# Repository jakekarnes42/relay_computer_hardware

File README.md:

# Relay Computer (Hardware)
This repo contains the hardware information for a computer constructed out of relays. Its software companion project can be found [here](https://github.com/jakekarnes42/relay_computer_software). 

This project has taken much of its inspiration from Dr. Harry Porter's [relay computer](https://web.cecs.pdx.edu/~harry/Relay/RelayPaper.htm). While there are many architectural similarities, there are also significant differences which are described below. This project wouldn't have been possible for me without his clear notes and thorough explanations. 

The documentation is still a work in progress and likely to change as the design itself changes. 

## Hardware Architecture Notes:
### Registers:
All registers are 16 bits (1 word) wide. There are 11 registers total.

There are 5 general purpose registers: AX, BX, CX, DX, and EX. These registers don’t have any special functions (e.g. stack operations). 

There are 2 stack-pointer registers: SP and RP. These are used with the PUSH, POP, CALL and CALL_I operations. These registers point to memory locations of the current top of the stack. When a value is pushed onto the stack, the register is first incremented, and then the value is copied to that location in memory. When a value is to popped off the stack, the value in the memory address pointed to by the stack register is returned, and then the stack register is decremented. 

There is one program counter: PC. The PC contains the address of the next
instruction to be executed. In some computers, this register is called the “Instruction Pointer”.

There is one instruction register: INST. During instruction execution, INST contains the current instruction being executed.

There are two temporary registers: TMP1 and TMP2. These are considered “scratch pads” and their values are not to be considered consistent between instructions. These are the inputs to the ALU. 
### Condition Codes:
####  Zero: 
True (1) when the ALU output is zero. If any bit of the ALU output is 1, then this flag will be set to false (0).
Sign:
True (1) when the highest (16th) bit of the ALU output is 1. That is, if considered as a signed value, the flag is set to true when the ALU output is negative. 
#### Overflow:
True (1) when the ALU output produced a signed overflow. Overflow occurs if the addition of two positive numbers gives a negative number and if the addition of two negative numbers gives a positive. That is, you need to compare the MSB of the operands and the answer. If the sign of the operands and the sign of the answer don't match, the overflow flag is turned on. The output is too large or too small to store in 16 bits (using two’s-complement format)

If the ALU isn’t performing ADD, INC, or DEC, this should be false (0), since it doesn’t really make sense for a logic operation to result in overflow
#### Carry:
This is the value of the 17th bit of the output. If performing unsigned addition, this indicates that the result was too large to fit into a 16-bit word (i.e. too large to fit into a register). If performing subtraction (e.g. a−b), the carry bit is equivalent to a < b.

If the ALU isn’t performing ADD, INC, or DEC, this should be false (0).
Memory:
The computer has 1,048,576 bits (1 Mb) of random access memory. This is organized as 65,536 (64k) words of 16 bits each. This results in 16-bit addresses, each storing a 16-bit word. 

The memory is non-volatile, i.e. the memory isn’t cleared when the computer is powered off. The program can be loaded into memory separately before the computer is powered on. 
#### ALU:
The ALU takes 3 inputs: a 3-bit function code, and two 16-bit operands. The ALU produces 5 outputs: the zero flag, the sign flag, the overflow flag, the carry flag, and a 16-bit result. 

The 3 bit function code is interpreted as follows:
* 000: INC
* 001: DEC
* 010: ADD
* 011: AND
* 100: OR
* 101: XOR
* 110: NOT
* 111: SHL

##### Design: 

## Changes from Harry’s Design
### Definite
* Dedicated stack register(s)
* I/O device support
* Four ALU-set flags:
1.  s (sign)
2.  z (zero)
3. c (carry)
4.  o (overflow) ** ← NEW**
### Maybe
* TMP registers?
   These aren’t addressable by themselves, but are intermediates for other operations. For example, two TMP registers could be used as the inputs to the ALU. The real operand(s) would be moved into the TMP registers before the ALU is engaged
* Split ALU: single operand instructions vs double operand instructions
   The Arithmetic side should support ADD, INC, DEC. These can all use the Zuse adder with different input C, or 1, or -1
   The Logic side should support AND, OR, XOR, NOT, ROL

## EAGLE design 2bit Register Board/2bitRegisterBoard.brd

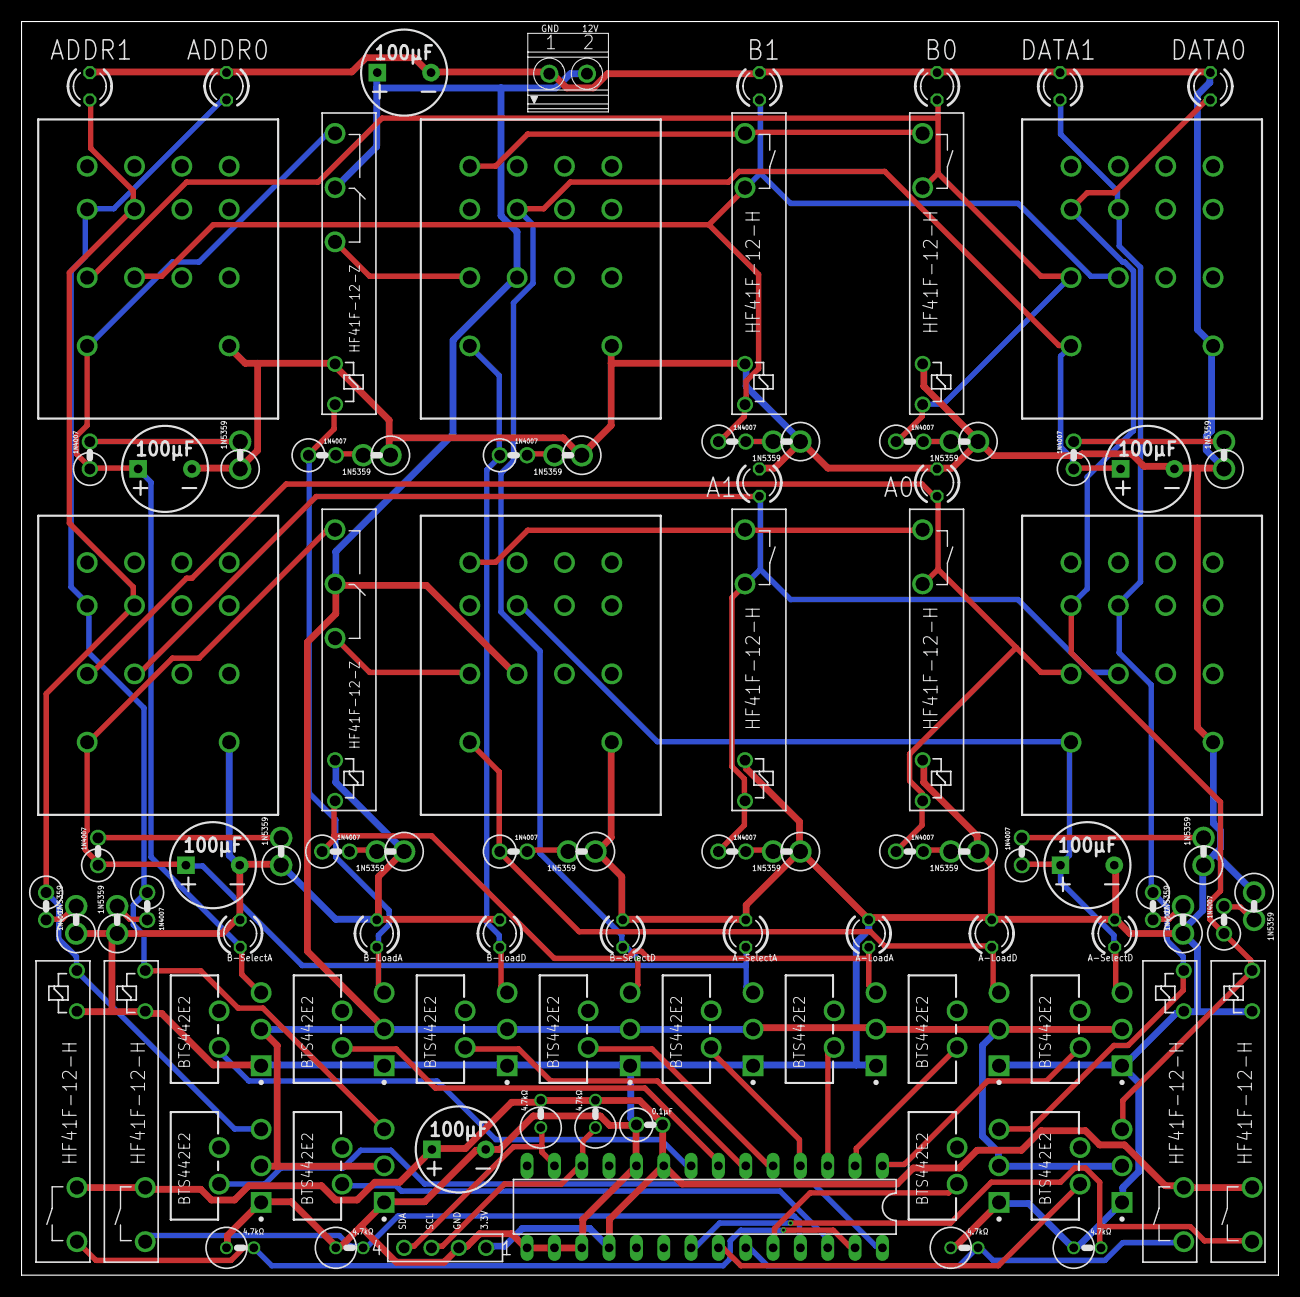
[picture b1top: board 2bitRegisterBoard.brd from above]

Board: 2 copper layers, 116.8 x 116.5 mm, 92 parts (0 on the bottom side), 57 nets.

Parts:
12V_PWR_BLK:C1: 100uF; CPOL-RADIAL-5MM-8MM
12V_PWR_BLK:PWR: PWR_BLK; 1751248
COMP_SIGNALS1:3V3_TO_12_1BIT0:U1, COMP_SIGNALS1:3V3_TO_12_1BIT1:U1, COMP_SIGNALS1:3V3_TO_12_1BIT2:U1, COMP_SIGNALS1:3V3_TO_12_1BIT3:U1, COMP_SIGNALS1:3V3_TO_12_1BIT4:U1, COMP_SIGNALS1:3V3_TO_12_1BIT5:U1, COMP_SIGNALS1:3V3_TO_12_1BIT6:U1, COMP_SIGNALS1:3V3_TO_12_1BIT7:U1, COMP_SIGNALS1:DUAL_12V⇆3V3_1BIT0:3V3_TO_12_1BIT1:U1, COMP_SIGNALS1:DUAL_12V⇆3V3_1BIT1:3V3_TO_12_1BIT1:U1, COMP_SIGNALS1:DUAL_12V⇆3V3_1BIT2:3V3_TO_12_1BIT1:U1, COMP_SIGNALS1:DUAL_12V⇆3V3_1BIT3:3V3_TO_12_1BIT1:U1: BTS442E2; TO170P440X1000X1975-5B
COMP_SIGNALS1:DUAL_12V⇆3V3_1BIT0:12V_TO_3V3_1BIT1:D5, COMP_SIGNALS1:DUAL_12V⇆3V3_1BIT1:12V_TO_3V3_1BIT1:D5, COMP_SIGNALS1:DUAL_12V⇆3V3_1BIT2:12V_TO_3V3_1BIT1:D5, COMP_SIGNALS1:DUAL_12V⇆3V3_1BIT3:12V_TO_3V3_1BIT1:D5: 1N4007; RAD2,5
COMP_SIGNALS1:DUAL_12V⇆3V3_1BIT0:12V_TO_3V3_1BIT1:D6, COMP_SIGNALS1:DUAL_12V⇆3V3_1BIT1:12V_TO_3V3_1BIT1:D6, COMP_SIGNALS1:DUAL_12V⇆3V3_1BIT2:12V_TO_3V3_1BIT1:D6, COMP_SIGNALS1:DUAL_12V⇆3V3_1BIT3:12V_TO_3V3_1BIT1:D6: 1N5359VERT_SML; RAD2.5_D2
COMP_SIGNALS1:DUAL_12V⇆3V3_1BIT0:12V_TO_3V3_1BIT1:K3, COMP_SIGNALS1:DUAL_12V⇆3V3_1BIT1:12V_TO_3V3_1BIT1:K3, COMP_SIGNALS1:DUAL_12V⇆3V3_1BIT2:12V_TO_3V3_1BIT1:K3, COMP_SIGNALS1:DUAL_12V⇆3V3_1BIT3:12V_TO_3V3_1BIT1:K3: HF41F-12-H
COMP_SIGNALS1:I2C_IO:C1: 100uF; CPOL-RADIAL-5MM-8MM
COMP_SIGNALS1:I2C_IO:C2: 0.1UF; VERT_CAP
COMP_SIGNALS1:I2C_IO:IC1: MCP23017SP; DIL28-3
COMP_SIGNALS1:I2C_IO:R1, COMP_SIGNALS1:I2C_IO:R2, COMP_SIGNALS1:I2C_IO:R3, COMP_SIGNALS1:I2C_IO:R4, COMP_SIGNALS1:I2C_IO:R5, COMP_SIGNALS1:I2C_IO:R6: 4.7KOHM; RAD2.5_RES
COMP_SIGNALS1:I2C_IO:SV1: FE04-1
COMP_SIGNALS1:LED0, COMP_SIGNALS1:LED1, COMP_SIGNALS1:LED2, COMP_SIGNALS1:LED3, COMP_SIGNALS1:LED4, COMP_SIGNALS1:LED5, COMP_SIGNALS1:LED6, COMP_SIGNALS1:LED7, COMP_SIGNALS1:LED8, COMP_SIGNALS1:LED9, COMP_SIGNALS1:LED10, COMP_SIGNALS1:LED11: LED3MM
REGISTER_A:C1, REGISTER_A:C2: 100uF; CPOL-RADIAL-5MM-8MM
REGISTER_A:D1, REGISTER_A:D3, REGISTER_A:D7, REGISTER_A:D9: 1N4007; RAD2,5
REGISTER_A:D2, REGISTER_A:D4, REGISTER_A:D8, REGISTER_A:D10: 1N5359VERT_SML; RAD2.5_D2
REGISTER_A:ENABLE_ADDRESS:D1: 1N4007; RAD2,5
REGISTER_A:ENABLE_ADDRESS:D2: 1N5359VERT_SML; RAD2.5_D2
REGISTER_A:ENABLE_ADDRESS:K1: PY14-02
REGISTER_A:ENABLE_DATA:D1: 1N4007; RAD2,5
REGISTER_A:ENABLE_DATA:D2: 1N5359VERT_SML; RAD2.5_D2
REGISTER_A:ENABLE_DATA:K1: PY14-02
REGISTER_A:K1: HF41F-12-Z
REGISTER_A:K2: PY14-02
REGISTER_A:K4, REGISTER_A:K5: HF41F-12-H
REGISTER_A:LED2, REGISTER_A:LED3: LED3MM
REGISTER_B:C1, REGISTER_B:C2: 100uF; CPOL-RADIAL-5MM-8MM
REGISTER_B:D1, REGISTER_B:D3, REGISTER_B:D7, REGISTER_B:D9: 1N4007; RAD2,5
REGISTER_B:D2, REGISTER_B:D4, REGISTER_B:D8, REGISTER_B:D10: 1N5359VERT_SML; RAD2.5_D2
REGISTER_B:ENABLE_ADDRESS:D1: 1N4007; RAD2,5
REGISTER_B:ENABLE_ADDRESS:D2: 1N5359VERT_SML; RAD2.5_D2
REGISTER_B:ENABLE_ADDRESS:K1: PY14-02
REGISTER_B:ENABLE_DATA:D1: 1N4007; RAD2,5
REGISTER_B:ENABLE_DATA:D2: 1N5359VERT_SML; RAD2.5_D2
REGISTER_B:ENABLE_DATA:K1: PY14-02
REGISTER_B:K1: HF41F-12-Z
REGISTER_B:K2: PY14-02
REGISTER_B:K4, REGISTER_B:K5: HF41F-12-H
REGISTER_B:LED2, REGISTER_B:LED3: LED3MM

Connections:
+3V3: COMP_SIGNALS1:DUAL_12V⇆3V3_1BIT0:12V_TO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.4, COMP_SIGNALS1:DUAL_12V⇆3V3_1BIT1:12V_TO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.4, COMP_SIGNALS1:DUAL_12V⇆3V3_1BIT2:12V_TO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.4, COMP_SIGNALS1:DUAL_12V⇆3V3_1BIT3:12V_TO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.4, COMP_SIGNALS1:I2C_IO:C1.1, COMP_SIGNALS1:I2C_IO:C2.A, COMP_SIGNALS1:I2C_IO:IC1.9, COMP_SIGNALS1:I2C_IO:IC1.18, COMP_SIGNALS1:I2C_IO:R1.A, COMP_SIGNALS1:I2C_IO:R2.A, COMP_SIGNALS1:I2C_IO:SV1.1
+12V: 12V_PWR_BLK:C1.1, 12V_PWR_BLK:PWR.2, COMP_SIGNALS1:3V3_TO_12_1BIT0:U1.3, COMP_SIGNALS1:3V3_TO_12_1BIT1:U1.3, COMP_SIGNALS1:3V3_TO_12_1BIT2:U1.3, COMP_SIGNALS1:3V3_TO_12_1BIT3:U1.3, COMP_SIGNALS1:3V3_TO_12_1BIT4:U1.3, COMP_SIGNALS1:3V3_TO_12_1BIT5:U1.3, COMP_SIGNALS1:3V3_TO_12_1BIT6:U1.3, COMP_SIGNALS1:3V3_TO_12_1BIT7:U1.3, COMP_SIGNALS1:DUAL_12V⇆3V3_1BIT0:3V3_TO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.3, COMP_SIGNALS1:DUAL_12V⇆3V3_1BIT1:3V3_TO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.3, COMP_SIGNALS1:DUAL_12V⇆3V3_1BIT2:3V3_TO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.3, COMP_SIGNALS1:DUAL_12V⇆3V3_1BIT3:3V3_TO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.3, REGISTER_A:K1.4, REGISTER_A:K2.31, REGISTER_B:K1.4, REGISTER_B:K2.31
A0: COMP_SIGNALS1:DUAL_12V⇆3V3_1BIT2:3V3_TO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.5, COMP_SIGNALS1:DUAL_12V⇆3V3_1BIT2:12V_TO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.C, COMP_SIGNALS1:DUAL_12V⇆3V3_1BIT2:12V_TO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.1, COMP_SIGNALS1:LED10.A, REGISTER_A:ENABLE_ADDRESS:K1.44, REGISTER_B:ENABLE_ADDRESS:K1.44
A1: COMP_SIGNALS1:DUAL_12V⇆3V3_1BIT3:3V3_TO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.5, COMP_SIGNALS1:DUAL_12V⇆3V3_1BIT3:12V_TO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.C, COMP_SIGNALS1:DUAL_12V⇆3V3_1BIT3:12V_TO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.1, COMP_SIGNALS1:LED11.A, REGISTER_A:ENABLE_ADDRESS:K1.34, REGISTER_B:ENABLE_ADDRESS:K1.34
COMP_SIGNALS1:DUAL_12V⇆3V3_1BIT0:12V_TO_3V3_1BIT1:D$3: COMP_SIGNALS1:DUAL_12V⇆3V3_1BIT0:12V_TO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.A, COMP_SIGNALS1:DUAL_12V⇆3V3_1BIT0:12V_TO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.A
COMP_SIGNALS1:DUAL_12V⇆3V3_1BIT1:12V_TO_3V3_1BIT1:D$3: COMP_SIGNALS1:DUAL_12V⇆3V3_1BIT1:12V_TO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.A, COMP_SIGNALS1:DUAL_12V⇆3V3_1BIT1:12V_TO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.A
COMP_SIGNALS1:DUAL_12V⇆3V3_1BIT2:12V_TO_3V3_1BIT1:D$3: COMP_SIGNALS1:DUAL_12V⇆3V3_1BIT2:12V_TO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.A, COMP_SIGNALS1:DUAL_12V⇆3V3_1BIT2:12V_TO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.A
COMP_SIGNALS1:DUAL_12V⇆3V3_1BIT3:12V_TO_3V3_1BIT1:D$3: COMP_SIGNALS1:DUAL_12V⇆3V3_1BIT3:12V_TO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.A, COMP_SIGNALS1:DUAL_12V⇆3V3_1BIT3:12V_TO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.A
COMP_SIGNALS1:I2C_IO:SCL: COMP_SIGNALS1:I2C_IO:IC1.12, COMP_SIGNALS1:I2C_IO:R1.C, COMP_SIGNALS1:I2C_IO:SV1.3
COMP_SIGNALS1:I2C_IO:SDA: COMP_SIGNALS1:I2C_IO:IC1.13, COMP_SIGNALS1:I2C_IO:R2.C, COMP_SIGNALS1:I2C_IO:SV1.4
COMP_SIGNALS1:N$5: COMP_SIGNALS1:DUAL_12V⇆3V3_1BIT3:3V3_TO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.2, COMP_SIGNALS1:I2C_IO:IC1.28
COMP_SIGNALS1:N$6: COMP_SIGNALS1:DUAL_12V⇆3V3_1BIT3:12V_TO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.5, COMP_SIGNALS1:I2C_IO:IC1.27, COMP_SIGNALS1:I2C_IO:R6.A
COMP_SIGNALS1:N$7: COMP_SIGNALS1:DUAL_12V⇆3V3_1BIT2:3V3_TO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.2, COMP_SIGNALS1:I2C_IO:IC1.26
COMP_SIGNALS1:N$8: COMP_SIGNALS1:DUAL_12V⇆3V3_1BIT2:12V_TO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.5, COMP_SIGNALS1:I2C_IO:IC1.25, COMP_SIGNALS1:I2C_IO:R5.A
COMP_SIGNALS1:N$9: COMP_SIGNALS1:DUAL_12V⇆3V3_1BIT1:3V3_TO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.2, COMP_SIGNALS1:I2C_IO:IC1.24
COMP_SIGNALS1:N$10: COMP_SIGNALS1:DUAL_12V⇆3V3_1BIT1:12V_TO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.5, COMP_SIGNALS1:I2C_IO:IC1.23, COMP_SIGNALS1:I2C_IO:R4.A
COMP_SIGNALS1:N$11: COMP_SIGNALS1:DUAL_12V⇆3V3_1BIT0:3V3_TO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.2, COMP_SIGNALS1:I2C_IO:IC1.22
COMP_SIGNALS1:N$12: COMP_SIGNALS1:DUAL_12V⇆3V3_1BIT0:12V_TO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.5, COMP_SIGNALS1:I2C_IO:IC1.21, COMP_SIGNALS1:I2C_IO:R3.A
COMP_SIGNALS1:N$13: COMP_SIGNALS1:3V3_TO_12_1BIT7:U1.2, COMP_SIGNALS1:I2C_IO:IC1.8
COMP_SIGNALS1:N$14: COMP_SIGNALS1:3V3_TO_12_1BIT6:U1.2, COMP_SIGNALS1:I2C_IO:IC1.7
COMP_SIGNALS1:N$15: COMP_SIGNALS1:3V3_TO_12_1BIT5:U1.2, COMP_SIGNALS1:I2C_IO:IC1.6
COMP_SIGNALS1:N$16: COMP_SIGNALS1:3V3_TO_12_1BIT4:U1.2, COMP_SIGNALS1:I2C_IO:IC1.5
COMP_SIGNALS1:N$17: COMP_SIGNALS1:3V3_TO_12_1BIT3:U1.2, COMP_SIGNALS1:I2C_IO:IC1.4
COMP_SIGNALS1:N$18: COMP_SIGNALS1:3V3_TO_12_1BIT2:U1.2, COMP_SIGNALS1:I2C_IO:IC1.3
COMP_SIGNALS1:N$19: COMP_SIGNALS1:3V3_TO_12_1BIT1:U1.2, COMP_SIGNALS1:I2C_IO:IC1.2
COMP_SIGNALS1:N$20: COMP_SIGNALS1:3V3_TO_12_1BIT0:U1.2, COMP_SIGNALS1:I2C_IO:IC1.1
D0: COMP_SIGNALS1:DUAL_12V⇆3V3_1BIT0:3V3_TO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.5, COMP_SIGNALS1:DUAL_12V⇆3V3_1BIT0:12V_TO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.C, COMP_SIGNALS1:DUAL_12V⇆3V3_1BIT0:12V_TO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.1, COMP_SIGNALS1:LED8.A, REGISTER_A:ENABLE_DATA:K1.44, REGISTER_B:ENABLE_DATA:K1.44
D1: COMP_SIGNALS1:DUAL_12V⇆3V3_1BIT1:3V3_TO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.5, COMP_SIGNALS1:DUAL_12V⇆3V3_1BIT1:12V_TO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.C, COMP_SIGNALS1:DUAL_12V⇆3V3_1BIT1:12V_TO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.1, COMP_SIGNALS1:LED9.A, REGISTER_A:ENABLE_DATA:K1.34, REGISTER_B:ENABLE_DATA:K1.34
GND: 12V_PWR_BLK:C1.2, 12V_PWR_BLK:PWR.1, COMP_SIGNALS1:3V3_TO_12_1BIT0:U1.1, COMP_SIGNALS1:3V3_TO_12_1BIT1:U1.1, COMP_SIGNALS1:3V3_TO_12_1BIT2:U1.1, COMP_SIGNALS1:3V3_TO_12_1BIT3:U1.1, COMP_SIGNALS1:3V3_TO_12_1BIT4:U1.1, COMP_SIGNALS1:3V3_TO_12_1BIT5:U1.1, COMP_SIGNALS1:3V3_TO_12_1BIT6:U1.1, COMP_SIGNALS1:3V3_TO_12_1BIT7:U1.1, COMP_SIGNALS1:DUAL_12V⇆3V3_1BIT0:3V3_TO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.1, COMP_SIGNALS1:DUAL_12V⇆3V3_1BIT0:12V_TO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.C, COMP_SIGNALS1:DUAL_12V⇆3V3_1BIT0:12V_TO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.2, COMP_SIGNALS1:DUAL_12V⇆3V3_1BIT1:3V3_TO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.1, COMP_SIGNALS1:DUAL_12V⇆3V3_1BIT1:12V_TO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.C, COMP_SIGNALS1:DUAL_12V⇆3V3_1BIT1:12V_TO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.2, COMP_SIGNALS1:DUAL_12V⇆3V3_1BIT2:3V3_TO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.1, COMP_SIGNALS1:DUAL_12V⇆3V3_1BIT2:12V_TO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.C, COMP_SIGNALS1:DUAL_12V⇆3V3_1BIT2:12V_TO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.2, COMP_SIGNALS1:DUAL_12V⇆3V3_1BIT3:3V3_TO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.1, COMP_SIGNALS1:DUAL_12V⇆3V3_1BIT3:12V_TO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.C, COMP_SIGNALS1:DUAL_12V⇆3V3_1BIT3:12V_TO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.2, COMP_SIGNALS1:I2C_IO:C1.2, COMP_SIGNALS1:I2C_IO:C2.C, COMP_SIGNALS1:I2C_IO:IC1.10, COMP_SIGNALS1:I2C_IO:IC1.15, COMP_SIGNALS1:I2C_IO:IC1.16, COMP_SIGNALS1:I2C_IO:IC1.17, COMP_SIGNALS1:I2C_IO:R3.C, COMP_SIGNALS1:I2C_IO:R4.C, COMP_SIGNALS1:I2C_IO:R5.C, COMP_SIGNALS1:I2C_IO:R6.C, COMP_SIGNALS1:I2C_IO:SV1.2, COMP_SIGNALS1:LED0.K, COMP_SIGNALS1:LED1.K, COMP_SIGNALS1:LED2.K, COMP_SIGNALS1:LED3.K, COMP_SIGNALS1:LED4.K, COMP_SIGNALS1:LED5.K, COMP_SIGNALS1:LED6.K, COMP_SIGNALS1:LED7.K, COMP_SIGNALS1:LED8.K, COMP_SIGNALS1:LED9.K, COMP_SIGNALS1:LED10.K, COMP_SIGNALS1:LED11.K, REGISTER_A:C1.2, REGISTER_A:C2.2, REGISTER_A:D2.C, REGISTER_A:D4.C, REGISTER_A:D8.C, REGISTER_A:D10.C, REGISTER_A:ENABLE_ADDRESS:D2.C, REGISTER_A:ENABLE_ADDRESS:K1.A1, REGISTER_A:ENABLE_DATA:D2.C, REGISTER_A:ENABLE_DATA:K1.A1, REGISTER_A:K1.2, REGISTER_A:K2.A1, REGISTER_A:K4.2, REGISTER_A:K5.2, REGISTER_A:LED2.K, REGISTER_A:LED3.K, REGISTER_B:C1.2, REGISTER_B:C2.2, REGISTER_B:D2.C, REGISTER_B:D4.C, REGISTER_B:D8.C, REGISTER_B:D10.C, REGISTER_B:ENABLE_ADDRESS:D2.C, REGISTER_B:ENABLE_ADDRESS:K1.A1, REGISTER_B:ENABLE_DATA:D2.C, REGISTER_B:ENABLE_DATA:K1.A1, REGISTER_B:K1.2, REGISTER_B:K2.A1, REGISTER_B:K4.2, REGISTER_B:K5.2, REGISTER_B:LED2.K, REGISTER_B:LED3.K
R0_LOADA: COMP_SIGNALS1:3V3_TO_12_1BIT2:U1.5, COMP_SIGNALS1:LED2.A, REGISTER_A:D1.C, REGISTER_A:K1.1
R0_LOADD: COMP_SIGNALS1:3V3_TO_12_1BIT1:U1.5, COMP_SIGNALS1:LED1.A, REGISTER_A:D3.C, REGISTER_A:K2.A2
R0_SELECTA: COMP_SIGNALS1:3V3_TO_12_1BIT3:U1.5, COMP_SIGNALS1:LED3.A, REGISTER_A:C1.1, REGISTER_A:ENABLE_ADDRESS:D1.C, REGISTER_A:ENABLE_ADDRESS:K1.A2, REGISTER_A:K1.5
R0_SELECTD: COMP_SIGNALS1:3V3_TO_12_1BIT0:U1.5, COMP_SIGNALS1:LED0.A, REGISTER_A:C2.1, REGISTER_A:ENABLE_DATA:D1.C, REGISTER_A:ENABLE_DATA:K1.A2, REGISTER_A:K2.34
R1_LOADA: COMP_SIGNALS1:3V3_TO_12_1BIT6:U1.5, COMP_SIGNALS1:LED6.A, REGISTER_B:D1.C, REGISTER_B:K1.1
R1_LOADD: COMP_SIGNALS1:3V3_TO_12_1BIT5:U1.5, COMP_SIGNALS1:LED5.A, REGISTER_B:D3.C, REGISTER_B:K2.A2
R1_SELECTA: COMP_SIGNALS1:3V3_TO_12_1BIT7:U1.5, COMP_SIGNALS1:LED7.A, REGISTER_B:C1.1, REGISTER_B:ENABLE_ADDRESS:D1.C, REGISTER_B:ENABLE_ADDRESS:K1.A2, REGISTER_B:K1.5
R1_SELECTD: COMP_SIGNALS1:3V3_TO_12_1BIT4:U1.5, COMP_SIGNALS1:LED4.A, REGISTER_B:C2.1, REGISTER_B:ENABLE_DATA:D1.C, REGISTER_B:ENABLE_DATA:K1.A2, REGISTER_B:K2.34
REGISTER_A:D$1: REGISTER_A:D1.A, REGISTER_A:D2.A
REGISTER_A:D$2: REGISTER_A:D3.A, REGISTER_A:D4.A
REGISTER_A:D$4: REGISTER_A:D7.A, REGISTER_A:D8.A
REGISTER_A:D$5: REGISTER_A:D9.A, REGISTER_A:D10.A
REGISTER_A:ENABLE_ADDRESS:D$1: REGISTER_A:ENABLE_ADDRESS:D1.A, REGISTER_A:ENABLE_ADDRESS:D2.A
REGISTER_A:ENABLE_DATA:D$1: REGISTER_A:ENABLE_DATA:D1.A, REGISTER_A:ENABLE_DATA:D2.A
REGISTER_A:HOLD: REGISTER_A:K2.42, REGISTER_A:K4.5, REGISTER_A:K5.5
REGISTER_A:N$1: REGISTER_A:K1.3, REGISTER_A:K2.41
REGISTER_A:R0: REGISTER_A:D9.C, REGISTER_A:ENABLE_ADDRESS:K1.41, REGISTER_A:ENABLE_DATA:K1.41, REGISTER_A:K5.1, REGISTER_A:K5.4, REGISTER_A:LED2.A
REGISTER_A:R1: REGISTER_A:D7.C, REGISTER_A:ENABLE_ADDRESS:K1.31, REGISTER_A:ENABLE_DATA:K1.31, REGISTER_A:K4.1, REGISTER_A:K4.4, REGISTER_A:LED3.A
REGISTER_B:D$1: REGISTER_B:D1.A, REGISTER_B:D2.A
REGISTER_B:D$2: REGISTER_B:D3.A, REGISTER_B:D4.A
REGISTER_B:D$4: REGISTER_B:D7.A, REGISTER_B:D8.A
REGISTER_B:D$5: REGISTER_B:D9.A, REGISTER_B:D10.A
REGISTER_B:ENABLE_ADDRESS:D$1: REGISTER_B:ENABLE_ADDRESS:D1.A, REGISTER_B:ENABLE_ADDRESS:D2.A
REGISTER_B:ENABLE_DATA:D$1: REGISTER_B:ENABLE_DATA:D1.A, REGISTER_B:ENABLE_DATA:D2.A
REGISTER_B:HOLD: REGISTER_B:K2.42, REGISTER_B:K4.5, REGISTER_B:K5.5
REGISTER_B:N$1: REGISTER_B:K1.3, REGISTER_B:K2.41
REGISTER_B:R0: REGISTER_B:D9.C, REGISTER_B:ENABLE_ADDRESS:K1.41, REGISTER_B:ENABLE_DATA:K1.41, REGISTER_B:K5.1, REGISTER_B:K5.4, REGISTER_B:LED2.A
REGISTER_B:R1: REGISTER_B:D7.C, REGISTER_B:ENABLE_ADDRESS:K1.31, REGISTER_B:ENABLE_DATA:K1.31, REGISTER_B:K4.1, REGISTER_B:K4.4, REGISTER_B:LED3.A
